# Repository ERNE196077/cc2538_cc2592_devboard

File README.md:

# cc2538_cc2592_devboard
This board is small enough to fit in a breadboard and let one space for pin connectivity, some features are:
* APA102 2020 onboard.
* FTDI FT232 UART-USB transceiver onboard 
* SN74AHCT125 onboard for 5v TTL (PA5 & PA6)
* RP SMA Female connector for high gain antenna
* Power consumption with LED working and SPI trasmitting each 100 ms = 0.05 A
* Dedicated Flash (PA2) and Reset buttons. 

## Flashing instructions for OpenThread
I'm using the cc2538-bsl.py script from JelmerT to flash the board. All the recognitions goes to him: 
[cc2538-bsl](https://github.com/JelmerT/cc2538-bsl)

Set the bootloader in the board: Press Reset button while holding the Flash button.
Compile the cc2538 example as seen in the [OpenThread.io](https://openthread.io/guides/build) page.

*NOTE* Make sure to modify the dedicated pins in the file /examples/platforms/cc2538/startup-gcc.c to match the above ones.

Convert to binary the resulting image
```
arm-none-eabi-objcopy -O binary output/cc2538/bin/ot-cli-ftd output/cc2538/bin/ot-cli-ftd.bin
```
Flash the image
```
sudo python ./cc2538-bsl/cc2538-bsl.py -p /dev/ttyUSB0 -b 115200 -e -w -v -V  output/cc2538/bin/ot-cli-ftd.bin
```

## KICAD dependencies 
Make sure to update your KICAD and update the libraries. Then you will need to link and match the footprints and schematic components.

## Libraries

Most of the work done with this board has been based in the OpenThread project, but custom libraries are available to fit the capabilities of this board:
[OpenThread](https://github.com/openthread/openthread)
[cc2538_cc2592_libs](https://github.com/ERNE196077/cc2538_cc2592_libs)

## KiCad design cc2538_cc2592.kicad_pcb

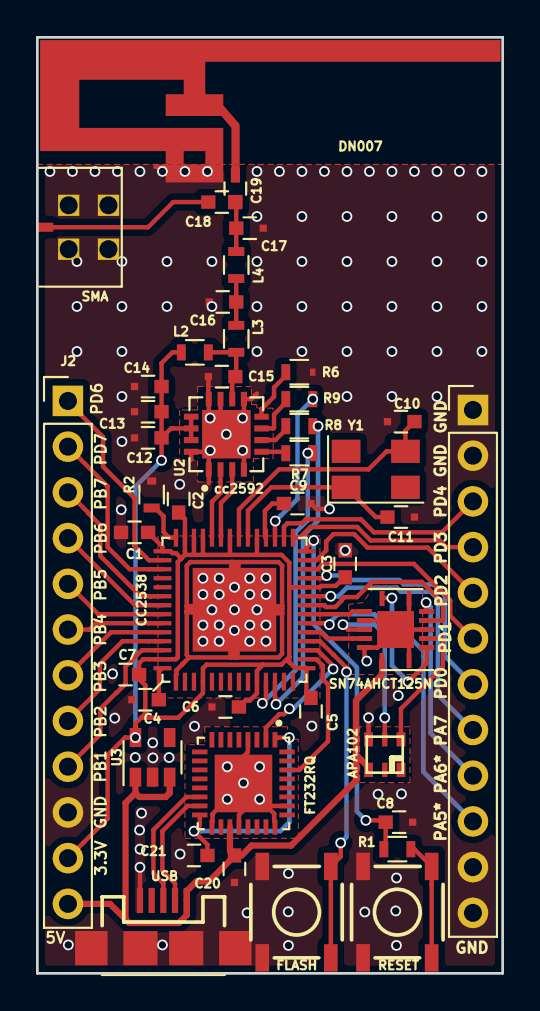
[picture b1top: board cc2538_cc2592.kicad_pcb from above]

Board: 2 copper layers, 25.9 x 52.0 mm, 44 parts (0 on the bottom side), 53 nets.

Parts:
APA102: APA102; APA102-2020
C1, C2, C3, C5, C6, C21: 0.1uF; C_0603
C4, C7, C9, C12: 1uF; C_0603
C8, C13: 1nF; C_0603
C10, C11: 47pF; C_0603
C14: 12pF; C_0603
C15, C16: 2.2pF; C_0603
C17: 0.2pF; C_0603
C18, C19: 18pF; C_0603
C20: 10nF; C_0603
CC2538: CC2538; QFN56
DN007: Antenna; Texas_DN007
J2: H1; Pin_Header_Straight_1x12_Pitch2.54mm
J3: H2; Pin_Header_Straight_1x12_Pitch2.54mm
L2: 4.7nH; L_0603
L3: 1nH; L_0603
L4: 2nH; L_0603
R1: 2.2; R_0603
R2: 56K; R_0603
R6: 3.9K; R_0603
R7, R8, R9: 10K; R_0603
SMA: SMA; MOLEX_SMA_F_3460
SN74AHCT125N: SN74AHCT125N; Texas_S-PVQFN-N14
SW1: RESET; TACTILE_SWITCH_SMD
SW2: FLASH; TACTILE_SWITCH_SMD
U2: cc2592; QFN65P400X400X100-17N
U3: LP5907QMFX; SOT-23-5
U4: FT232RQ; QFN50P500X500X100-33N
USB1: USB; USB-MICROB
Y1: 32Mhz; Crystal_SMD_5032-4pin_5.0x3.2mm

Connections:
+3.3V: C1.1, C2.1, C3.1, C5.1, C6.1, C7.1, C12.1, C13.1, C14.1, CC2538.4, CC2538.10, CC2538.15, CC2538.24, CC2538.33, CC2538.36, CC2538.39, CC2538.40, CC2538.41, CC2538.43, CC2538.55, J2.11, L2.1, U2.13, U2.14, U2.15, U3.5
+5V: APA102.5, C20.2, J2.12, SN74AHCT125N.14, U3.1, U3.3, U4.19, USB1.VBUS
GND: APA102.4, C1.2, C2.2, C3.2, C4.1, C5.2, C6.2, C7.2, C8.1, C9.1, C10.1, C11.1, C12.2, C13.2, C14.2, C15.2, C16.2, C17.2, C20.1, C21.2, CC2538.1, CC2538.PAD, DN007.GND, J2.10, J3.1, J3.2, J3.11, J3.12, R2.1, R6.2, SMA.GND, SN74AHCT125N.1, SN74AHCT125N.4, SN74AHCT125N.7, SN74AHCT125N.10, SN74AHCT125N.13, SN74AHCT125N.15, SW1.3, SW1.4, SW2.3, SW2.4, U2.1, U2.4, U2.9, U2.11, U2.12, U2.16, U2.17, U3.2, U4.4, U4.17, U4.20, U4.24, U4.26, U4.33, USB1.GND
unnamed: C19.2, DN007.1
unnamed: C4.2, CC2538.56
unnamed: C8.2, CC2538.28, R1.1
unnamed: C9.2, CC2538.32
unnamed: C10.2, CC2538.35, Y1.3
unnamed: C11.2, CC2538.34, Y1.1
unnamed: C15.1, L2.2, L3.1, U2.10
unnamed: C16.1, L3.2, L4.1
unnamed: C17.1, C18.2, C19.1, L4.2
unnamed: C18.1, SMA.1
unnamed: C21.1, U4.1, U4.16
unnamed: APA102.2, SN74AHCT125N.3
unnamed: APA102.3, SN74AHCT125N.11
unnamed: R1.2, SW1.1, SW1.2
unnamed: CC2538.42, R2.2
unnamed: R6.1, U2.8
unnamed: R7.1, U2.5
unnamed: R8.1, U2.6
unnamed: R9.1, U2.7
unnamed: CC2538.18, SW2.1, SW2.2
unnamed: U4.14, USB1.D+
unnamed: U4.15, USB1.D-
PA3: CC2538.19, SN74AHCT125N.12
PA4: CC2538.20, SN74AHCT125N.2
PA5: CC2538.21, SN74AHCT125N.9
PA5*: J3.10, SN74AHCT125N.8
PA6: CC2538.22, SN74AHCT125N.5
PA6*: J3.9, SN74AHCT125N.6
PA7: CC2538.23, J3.8
PB1: CC2538.54, J2.9
PB2: CC2538.53, J2.8
PB3: CC2538.52, J2.7
PB4: CC2538.51, J2.6
PB5: CC2538.50, J2.5
PB6: CC2538.49, J2.4
PB7: CC2538.48, J2.3
PC2: CC2538.12, R8.2
PC3: CC2538.11, R7.2
PD0: CC2538.25, J3.7
PD1: CC2538.26, J3.6
PD2: CC2538.27, J3.5
PD3: CC2538.29, J3.4
PD4: CC2538.30, J3.3
PD5: CC2538.31, R9.2
PD6: CC2538.44, J2.1
PD7: CC2538.45, J2.2
RF_N_MCU: CC2538.38, U2.2
RF_P_MCU: CC2538.37, U2.3
RXD: CC2538.16, U4.30
TXD: CC2538.17, U4.2
